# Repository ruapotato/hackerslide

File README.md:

# HackerSlide 810

A pocketable Linux handheld in the spirit of the Nokia N810: landscape screen, slide-out QWERTY keyboard with a
D-pad, an off-the-shelf CM4-format compute module on a custom carrier board. Open hardware.

> **Direction change, 2026-11-27.** `main` is turning from a Linux handheld into a **hack pad**: the same slider
> body and thumb keyboard around a powerful microcontroller instead of a Linux module, built as a radio and hardware
> multi-tool (sub-GHz, NFC, software-defined radio as far as is reasonable), with its own firmware, MicroPython, and
> music and audiobook playback. See [decisions/0009](docs/decisions/0009-hack-pad.md). The Linux handheld described
> below is complete as a design and lives on the branch [`linux-handheld`](https://github.com/ruapotato/hackerslide/tree/linux-handheld);
> everything below this note still describes it until the new design replaces it.

**Status: rev 0.1 is designed and checked as far as it can be without parts. Nothing has been built or tested:
the first boards are the test.**

**These are renders.** The enclosure, the boards and their parts are drawn from the design files; the compute
module, the battery pack, the keycap legends and what the screen shows are drawn for the picture. 131.5 x 74 x
19.35 mm; a Nokia N810 is 14 mm thick ([comparison](mechanical/renders/compare_stack.png)).

## What it is

| | |
|---|---|
| Compute | LuckFox Core3566 (RK3566, 4x Cortex-A55), swappable for other CM4-format modules within limits |
| Display | 4.0" 480 x 800 IPS, capacitive touch |
| Keyboard | 48 keys + D-pad, tact switches, I2C scanner, slides out on rails with magnet detents |
| Battery | 2800 mAh pack, USB-C charging |
| I/O | USB-C, 3.5 mm headset jack, microSD, Wi-Fi/Bluetooth on the module |
| OS | Debian/Mobian on a mainline-ish kernel (not started) |

## Where things stand

| Part | State |
|---|---|
| Carrier board | Schematic audited and revised; **fully routed**, no DRC errors. Power blocks, USB and DSI pairs laid by hand in the generator, the rest by the repository's grid router. Checked by scripts and by independent AI reviewers ([review](docs/review-2026-11-25.md)), not by a person; not built |
| Keyboard board | **Fully routed**, no DRC errors. Checked the same way; not built |
| Top plate, keyboard flex cable | Complete |
| Enclosure | Parametric model, collision-checked, with rails, travel stop, hooks and button caps; print files and assembly steps in [printing](docs/printing.md). Not printed |
| Fabrication files | Generated on demand and verified against the board files by `gerber_check.py`; `order_files.py` packs them the way JLCPCB's order page takes them ([ordering guide](bom/ordering-guide.md)). Not committed, not sent anywhere |
| Cost | First prototype, working or not, about $820-1,200, an estimate from published fees with no quote ([purchasing](bom/purchasing.md)) |
| Battery | Jauch LP675365JU, 2800 mAh, in stock at DigiKey. It is rated 2 A, so the fuse is set to 1.86 A; it has no thermistor, so the carrier's own is fitted ([purchasing](bom/purchasing.md)) |
| Bring-up | Serial console, test pads on every rail, status lamps: [bring-up plan](docs/bring-up-plan.md), [test points](docs/test-points.md), [device-tree requirements](docs/device-tree.md) |

Start with [`docs/audit-status.md`](docs/audit-status.md), then [`docs/open-questions.md`](docs/open-questions.md).

## Documents

[requirements](docs/requirements.md) · [architecture](docs/architecture.md) ·
[decisions](docs/decisions/README.md) · [pin matrix](docs/compute-pin-matrix.md) ·
[power budget](docs/power-budget.md) · [thermal](docs/thermal.md) · [carrier board](docs/carrier-board.md) ·
[keyboard](docs/keyboard.md) · [enclosure](docs/enclosure.md) · [bring-up plan](docs/bring-up-plan.md) ·
[risks](docs/risks.md) · [roadmap](docs/roadmap.md) · [audit](docs/audit-2026-11-24.md) ·
[footprint review](docs/footprint-review.md) · [pre-fab review](docs/review-2026-11-25.md) · [test points](docs/test-points.md) ·
[device tree](docs/device-tree.md) · [routing status](docs/routing-status.md) · [BOM](bom/bom.csv) · [purchasing](bom/purchasing.md) ·
[fab orders](bom/fab-orders.md) · [thinner brain](docs/thinner-brain.md) · [ordering guide](bom/ordering-guide.md) · [printing](docs/printing.md)

## Regenerating everything

The boards and the enclosure are generated from Python. Needs KiCad 9 with its libraries, Python 3, CadQuery and
OpenSCAD; details in [`docs/HANDOFF.md`](docs/HANDOFF.md), section 2.

```sh
hardware/scripts/build_all.sh                               # libraries, schematics, boards, ERC/DRC
ROUTE=1 VENV=$PWD/.venv hardware/scripts/build_all.sh       # the same, plus routing (slow; venv needs scikit-image)
hardware/scripts/render_boards.sh                           # board renders
hardware/scripts/fab_outputs.sh hardware/carrier carrier /tmp/fab   # Gerbers, drill, placement (then gerber_check.py)
cd mechanical/src && ../../.venv/bin/python hackerslide.py  # enclosure, collision check
python3 render.py ..                                        # renders
python3 ../../bom/tools/make_bom.py                         # BOM with current JLCPCB prices
python3 ../../hardware/scripts/order_files.py               # order/: Gerber zips, BOM and placement files for JLCPCB
../render/assets.sh && ../render/render_all.sh OUT_DIR      # Blender stills and clips (see mechanical/render/scene.py)
```

## How to help

Review it. The questions we most want answered are in [`docs/open-questions.md`](docs/open-questions.md); the
things a hardware reviewer should check are in [`docs/carrier-board.md`](docs/carrier-board.md) and
[`docs/footprint-review.md`](docs/footprint-review.md). Open an issue.

## Licence

- **Hardware design** (`hardware/` and `mechanical/`: schematics, boards, libraries, enclosure models and their
  exported files) is licensed under the **CERN Open Hardware Licence Version 2 - Strongly Reciprocal**
  (CERN-OHL-S-2.0), see [`LICENSES/CERN-OHL-S-2.0.txt`](LICENSES/CERN-OHL-S-2.0.txt).
- **Software and documentation** (everything else, and the Python generator scripts inside `hardware/scripts/`
  and `mechanical/src/`, which are also covered as hardware source) are licensed under the **GNU Affero General
  Public License v3.0**, see [`LICENSE`](LICENSE).

Both are strong copyleft: anyone who distributes a modified design or a product made from it must publish their
source under the same terms.

Source location for CERN-OHL-S section 4: https://github.com/ruapotato/hackerslide

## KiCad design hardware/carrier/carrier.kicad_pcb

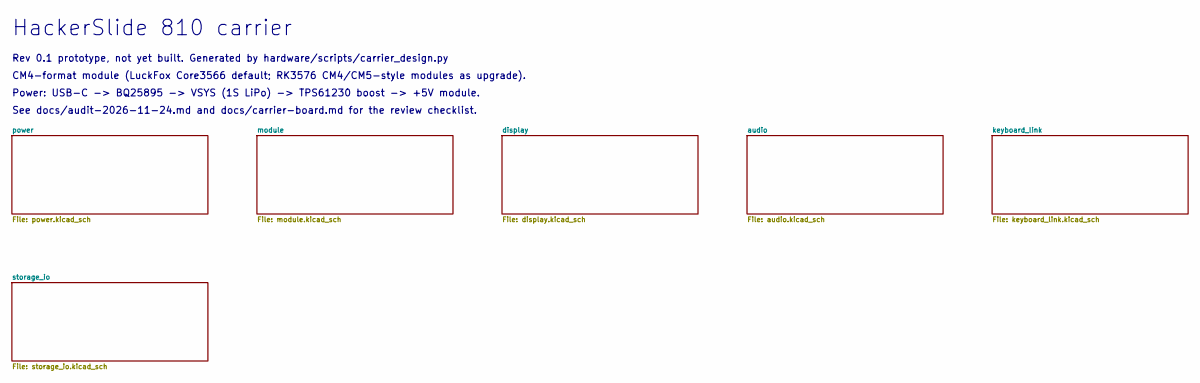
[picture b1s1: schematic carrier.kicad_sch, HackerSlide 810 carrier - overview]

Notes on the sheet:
HackerSlide 810 carrier
Rev 0.1 prototype, not yet built. Generated by hardware/scripts/carrier_design.py
CM4-format module (LuckFox Core3566 default; RK3576 CM4/CM5-style modules as upgrade).
Power: USB-C -> BQ25895 -> VSYS (1S LiPo) -> TPS61230 boost -> +5V module.
See docs/audit-2026-11-24.md and docs/carrier-board.md for the review checklist.

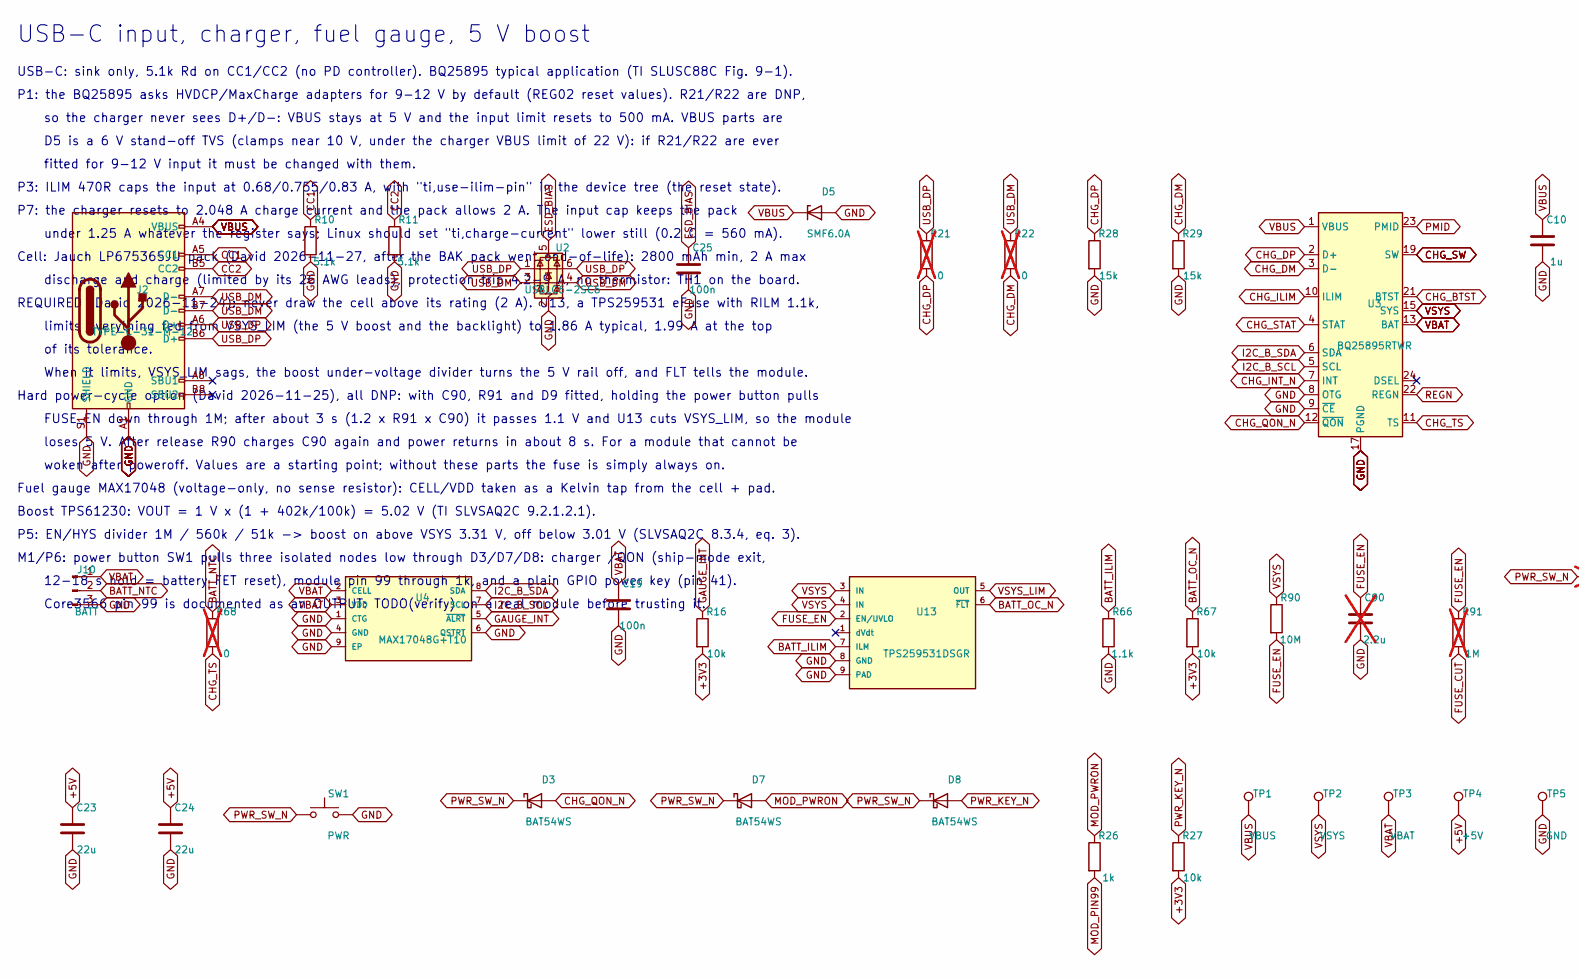
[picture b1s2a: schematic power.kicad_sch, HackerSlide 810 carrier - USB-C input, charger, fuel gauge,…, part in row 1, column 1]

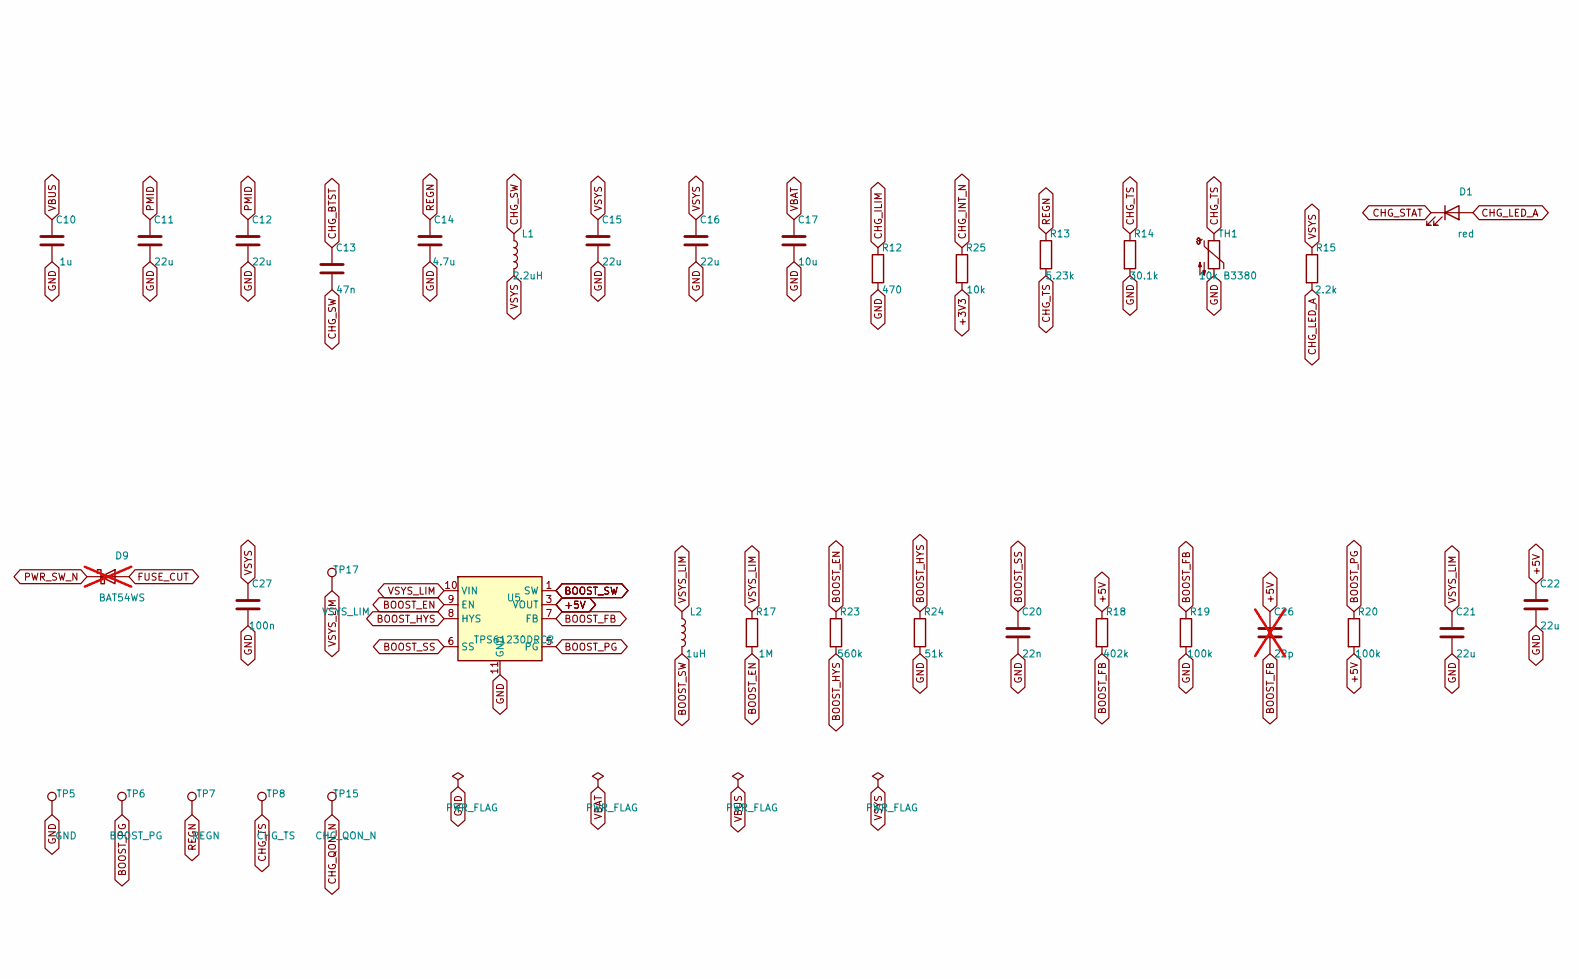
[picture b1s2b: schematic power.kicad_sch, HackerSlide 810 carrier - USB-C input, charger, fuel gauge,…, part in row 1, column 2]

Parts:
C10: 1u; C_0402_1005Metric; MPN CL05A105KA5NQNC; LCSC C52923
C11, C12, C15, C16, C21, C22, C23, C24: 22u; C_0805_2012Metric; MPN CL21A226MAQNNNE; LCSC C45783
C13: 47n; C_0402_1005Metric; MPN CL05B473KO5NNNC; LCSC C307434
C14: 4.7u; C_0603_1608Metric; MPN CL10A475KO8NNNC; LCSC C19666
C17: 10u; C_0603_1608Metric; MPN CL10A106KP8NNNC; LCSC C19702
C19, C25, C27: 100n; C_0402_1005Metric; MPN CL05B104KO5NNNC; LCSC C1525
C20: 22n; C_0402_1005Metric; MPN 0402B223K500NT; LCSC C1532
C26: 22p; C_0402_1005Metric; MPN 0402CG220J500NT; LCSC C1555; not fitted
C90: 2.2u; C_0402_1005Metric; MPN CL05A225MQ5NSNC; LCSC C12530; not fitted
D1: red; LED_0603_1608Metric; MPN KT-0603R; LCSC C2286
D3, D7, D8: BAT54WS; D_SOD-323; MPN BAT54WS-7-F; LCSC C124205
D5: SMF6.0A; D_SOD-123F; MPN SMF6.0A; LCSC C123790
D9: BAT54WS; D_SOD-323; MPN BAT54WS-7-F; LCSC C124205; not fitted
J2: TYPE-C-31-M-12; USB_C_Receptacle_HRO_TYPE-C-31-M-12; MPN TYPE-C-31-M-12; LCSC C165948
J10: BATT; Molex_SPOX_5268-03A_1x03_P2.50mm_Horizontal; MPN 22057035; LCSC C185225
L1: 2.2uH; L_Sunlord_MWSA0402S; MPN MWSA0402S-2R2MT; LCSC C408335
L2: 1uH; L_Sunlord_MWSA0402S; MPN MWSA0402S-1R0MT; LCSC C408332
R10, R11: 5.1k; R_0402_1005Metric; MPN 0402WGF5101TCE; LCSC C25905
R12: 470; R_0402_1005Metric; MPN 0402WGF4700TCE; LCSC C25117
R13: 5.23k; R_0402_1005Metric; MPN 0402WGF5231TCE; LCSC C25907
R14: 30.1k; R_0402_1005Metric; MPN 0402WGF3012TCE; LCSC C29402
R15: 2.2k; R_0402_1005Metric; MPN 0402WGF2201TCE; LCSC C25879
R16, R25, R27, R67: 10k; R_0402_1005Metric; MPN 0402WGF1002TCE; LCSC C25744
R17: 1M; R_0402_1005Metric; MPN 0402WGF1004TCE; LCSC C26083
R18: 402k; R_0402_1005Metric; MPN 0402WGF4023TCE; LCSC C25785
R19, R20: 100k; R_0402_1005Metric; MPN 0402WGF1003TCE; LCSC C25741
R21, R22, R68: 0; R_0402_1005Metric; MPN 0402WGF0000TCE; LCSC C17168; not fitted
R23: 560k; R_0402_1005Metric; MPN 0402WGF5603TCE; LCSC C132339
R24: 51k; R_0402_1005Metric; MPN 0402WGF5102TCE; LCSC C25794
R26: 1k; R_0402_1005Metric; MPN 0402WGF1001TCE; LCSC C11702
R28, R29: 15k; R_0402_1005Metric; MPN 0402WGF1502TCE; LCSC C25756
R66: 1.1k; R_0402_1005Metric; MPN 0402WGF1101TCE; LCSC C25860
R90: 10M; R_0402_1005Metric; MPN 0402WGF1005TCE; LCSC C26082
R91: 1M; R_0402_1005Metric; MPN 0402WGF1004TCE; LCSC C26083; not fitted
SW1: PWR; SW_SPST_EVQP7C; MPN EVQP7C01P; LCSC C388883
TH1: 10k B3380; R_0402_1005Metric; MPN NCP15XH103F03RC; LCSC C77131
TP1: VBUS; TestPoint_Pad_D1.0mm
TP2: VSYS; TestPoint_Pad_D1.0mm
TP3: VBAT; TestPoint_Pad_D1.0mm
TP4: +5V; TestPoint_Pad_D1.0mm
TP5: GND; TestPoint_Pad_D1.0mm
TP6: BOOST_PG; TestPoint_Pad_D1.0mm
TP7: REGN; TestPoint_Pad_D1.0mm
TP8: CHG_TS; TestPoint_Pad_D1.0mm
TP15: CHG_QON_N; TestPoint_Pad_D1.0mm
TP17: VSYS_LIM; TestPoint_Pad_D1.0mm
U2: USBLC6-2SC6; SOT-23-6; MPN USBLC6-2SC6; LCSC C7519
U3: BQ25895RTWR; Texas_RTW_WQFN-24-1EP_4x4mm_P0.5mm_EP2.7x2.7mm_ThermalVias; MPN BQ25895RTWR; LCSC C80200
U4: MAX17048G+T10; TDFN-8-1EP_2x2mm_P0.5mm_EP0.8x1.2mm; MPN MAX17048G+T10; LCSC C2682616
U5: TPS61230DRCR; Texas_S-PVSON-N10_ThermalVias; MPN TPS61230DRCR; LCSC C139626
U13: TPS259531DSGR; WSON-8-1EP_2x2mm_P0.5mm_EP0.9x1.6mm; MPN TPS259531DSGR; LCSC C2155674

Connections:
+3V3: R16.2, R25.2, R27.2, R67.2; also elsewhere on the board
+5V: C22.1, C23.1, C24.1, C26.1, R18.1, R20.2, TP4.1, U5.3 (VOUT), U5.4 (VOUT); also elsewhere on the board
BATT_ILIM: R66.1, U13.7 (ILM)
BATT_NTC: J10.2, R68.1
BATT_OC_N: R67.1, U13.6 (~FLT); also elsewhere on the board
BOOST_EN: R17.2, R23.1, U5.9 (EN)
BOOST_FB: C26.2, R18.2, R19.1, U5.7 (FB)
BOOST_HYS: R23.2, R24.1, U5.8 (HYS)
BOOST_PG: R20.1, TP6.1, U5.5 (PG)
BOOST_SS: C20.1, U5.6 (SS)
BOOST_SW: L2.2, U5.1 (SW), U5.2 (SW)
CC1: J2.A5 (CC1), R10.1
CC2: J2.B5 (CC2), R11.1
CHG_BTST: C13.1, U3.21 (BTST)
CHG_DM: R22.2, R29.1, U3.3 (D-)
CHG_DP: R21.2, R28.1, U3.2 (D+)
CHG_ILIM: R12.1, U3.10 (ILIM)
CHG_INT_N: R25.1, U3.7 (INT); also elsewhere on the board
CHG_LED_A: D1.2 (A), R15.2
CHG_QON_N: D3.2 (A), TP15.1, U3.12 (~QON)
CHG_STAT: D1.1 (K), U3.4 (STAT)
CHG_SW: C13.2, L1.1, U3.19 (SW), U3.20 (SW)
CHG_TS: R13.2, R14.1, R68.2, TH1.1, TP8.1, U3.11 (TS)
ESD_BIAS: C25.1, U2.5 (VBUS)
FUSE_CUT: D9.2 (A), R91.2
FUSE_EN: C90.1, R90.2, R91.1, U13.2 (EN/UVLO)
GAUGE_INT: R16.1, U4.5 (~ALRT); also elsewhere on the board
GND: C10.2, C11.2, C12.2, C14.2, C15.2, C16.2, C17.2, C19.2, C20.2, C21.2, C22.2, C23.2, C24.2, C25.2, C27.2, C90.2, D5.2 (A), J2.A1 (GND), J2.A12 (GND), J2.B1 (GND), J2.B12 (GND), J2.S1 (SHIELD), J10.3, R10.2, R11.2, R12.2, R14.2, R19.2, R24.2, R28.2, R29.2, R66.2, SW1.2, TH1.2, TP5.1, U2.2 (GND), U3.8 (OTG), U3.9 (~CE), U3.17 (PGND), U3.18 (PGND), U3.25 (PGND), U4.1 (CTG), U4.4 (GND), U4.6 (QSTRT), U4.9 (EP), U5.11 (GND), U13.8 (GND), U13.9 (PAD); also elsewhere on the board
I2C_B_SCL: U3.5 (SCL), U4.7 (SCL); also elsewhere on the board
I2C_B_SDA: U3.6 (SDA), U4.8 (SDA); also elsewhere on the board
MOD_PIN99: R26.2; also elsewhere on the board
MOD_PWRON: D7.2 (A), R26.1
PMID: C11.1, C12.1, U3.23 (PMID)
PWR_KEY_N: D8.2 (A), R27.1; also elsewhere on the board
PWR_SW_N: D3.1 (K), D7.1 (K), D8.1 (K), D9.1 (K), SW1.1
REGN: C14.1, R13.1, TP7.1, U3.22 (REGN)
USB_DM: J2.A7 (D-), J2.B7 (D-), R22.1, U2.3 (I/O2), U2.4 (I/O2); also elsewhere on the board
USB_DP: J2.A6 (D+), J2.B6 (D+), R21.1, U2.1 (I/O1), U2.6 (I/O1); also elsewhere on the board
VBAT: C17.1, C19.1, J10.1, TP3.1, U3.13 (BAT), U3.14 (BAT), U4.2 (CELL), U4.3 (VDD)
VBUS: C10.1, D5.1 (K), J2.A4 (VBUS), J2.A9 (VBUS), J2.B4 (VBUS), J2.B9 (VBUS), TP1.1, U3.1 (VBUS)
VSYS: C15.1, C16.1, C27.1, L1.2, R15.1, R90.1, TP2.1, U3.15 (SYS), U3.16 (SYS), U13.3 (IN), U13.4 (IN)
VSYS_LIM: C21.1, L2.1, R17.1, TP17.1, U5.10 (VIN), U13.5 (OUT); also elsewhere on the board

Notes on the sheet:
USB-C input, charger, fuel gauge, 5 V boost
USB-C: sink only, 5.1k Rd on CC1/CC2 (no PD controller). BQ25895 typical application (TI SLUSC88C Fig. 9-1).
P1: the BQ25895 asks HVDCP/MaxCharge adapters for 9-12 V by default (REG02 reset values). R21/R22 are DNP,
so the charger never sees D+/D-: VBUS stays at 5 V and the input limit resets to 500 mA. VBUS parts are
D5 is a 6 V stand-off TVS (clamps near 10 V, under the charger VBUS limit of 22 V): if R21/R22 are ever
fitted for 9-12 V input it must be changed with them.
P3: ILIM 470R caps the input at 0.68/0.755/0.83 A, with "ti,use-ilim-pin" in the device tree (the reset state).
P7: the charger resets to 2.048 A charge current and the pack allows 2 A. The input cap keeps the pack
under 1.25 A whatever the register says; Linux should set "ti,charge-current" lower still (0.2 C = 560 mA).
Cell: Jauch LP675365JU pack (David 2026-11-27, after the BAK pack went end-of-life): 2800 mAh min, 2 A max
discharge and charge (limited by its 26 AWG leads), protection trip 4.2-9 A, no thermistor: TH1 on the board.
REQUIRED (David 2026-11-24): never draw the cell above its rating (2 A). U13, a TPS259531 eFuse with RILM 1.1k,
limits everything fed from VSYS_LIM (the 5 V boost and the backlight) to 1.86 A typical, 1.99 A at the top
of its tolerance.
When it limits, VSYS_LIM sags, the boost under-voltage divider turns the 5 V rail off, and FLT tells the module.
Hard power-cycle option (David 2026-11-25), all DNP: with C90, R91 and D9 fitted, holding the power button pulls
FUSE_EN down through 1M; after about 3 s (1.2 x R91 x C90) it passes 1.1 V and U13 cuts VSYS_LIM, so the module
loses 5 V. After release R90 charges C90 again and power returns in about 8 s. For a module that cannot be
woken after poweroff. Values are a starting point; without these parts the fuse is simply always on.
Fuel gauge MAX17048 (voltage-only, no sense resistor): CELL/VDD taken as a Kelvin tap from the cell + pad.
Boost TPS61230: VOUT = 1 V x (1 + 402k/100k) = 5.02 V (TI SLVSAQ2C 9.2.1.2.1).
P5: EN/HYS divider 1M / 560k / 51k -> boost on above VSYS 3.31 V, off below 3.01 V (SLVSAQ2C 8.3.4, eq. 3).
M1/P6: power button SW1 pulls three isolated nodes low through D3/D7/D8: charger /QON (ship-mode exit,
12-18 s hold = battery FET reset), module pin 99 through 1k, and a plain GPIO power key (pin 41).
Core3566 pin 99 is documented as an OUTPUT: TODO(verify) on a real module before trusting it.

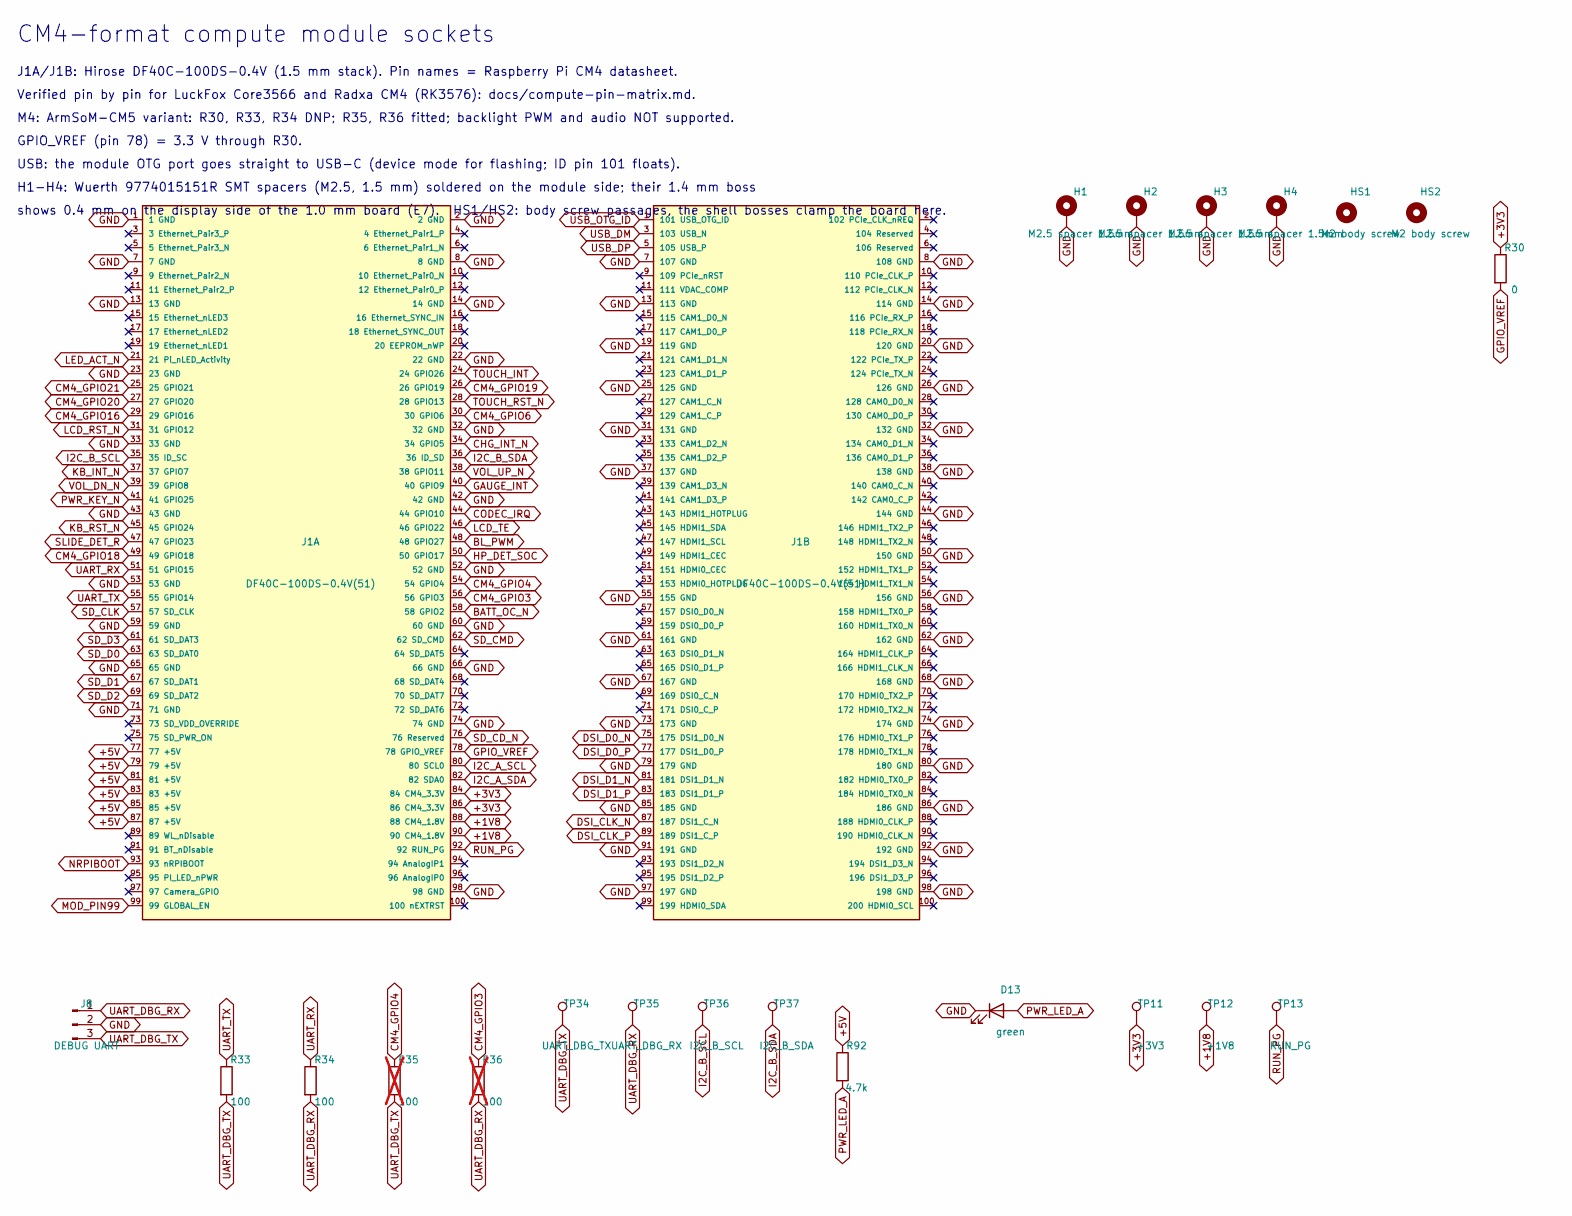
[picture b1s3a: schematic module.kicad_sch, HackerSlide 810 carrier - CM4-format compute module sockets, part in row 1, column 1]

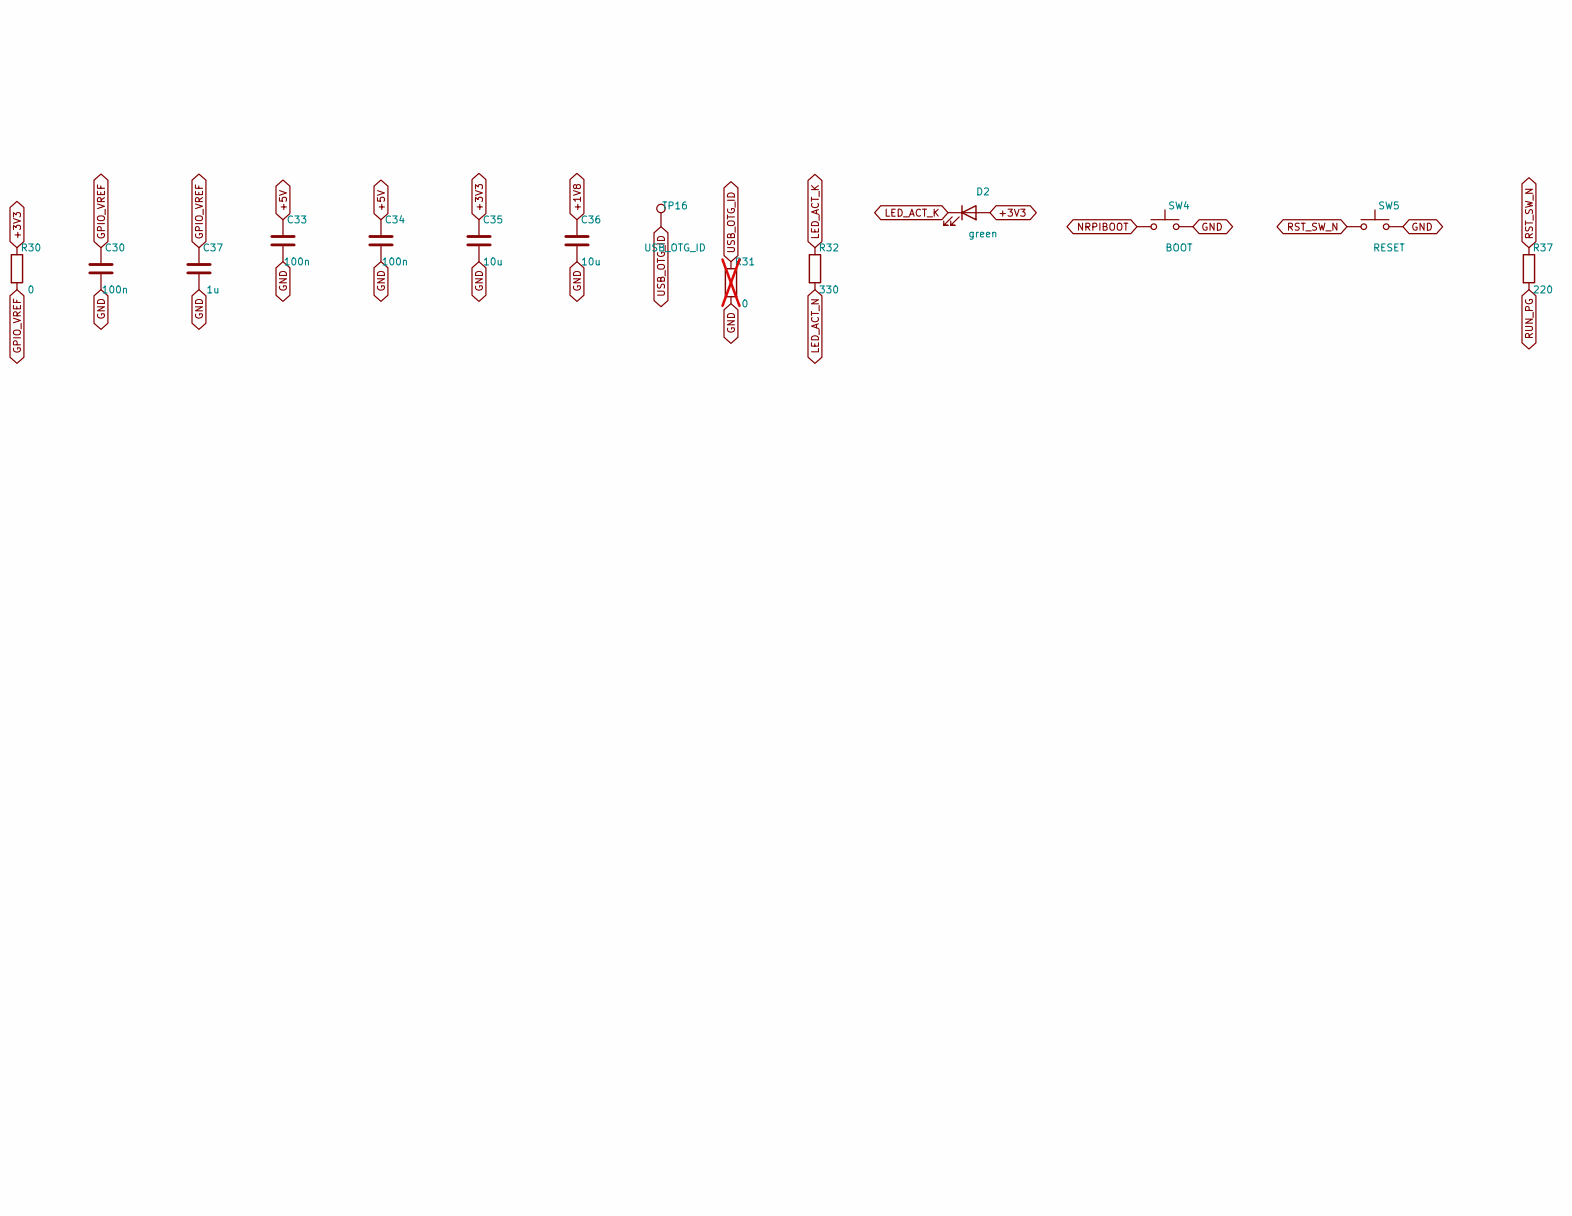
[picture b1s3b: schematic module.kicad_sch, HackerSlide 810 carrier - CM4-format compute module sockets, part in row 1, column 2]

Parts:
C30, C33, C34: 100n; C_0402_1005Metric; MPN CL05B104KO5NNNC; LCSC C1525
C35, C36: 10u; C_0603_1608Metric; MPN CL10A106KP8NNNC; LCSC C19702
C37: 1u; C_0402_1005Metric; MPN CL05A105KA5NQNC; LCSC C52923
D2, D13: green; LED_0603_1608Metric; MPN KT-0603G; LCSC C12624
H1, H2, H3, H4: M2.5 spacer 1.5mm; Mounting_Wuerth_WA-SMSI-M2.5_H1.5mm_9774015151R; MPN 9774015151R; LCSC C5353804
HS1, HS2: M2 body screw; MountingHole_M2_NPTH_BodyScrew
J1A, J1B: DF40C-100DS-0.4V(51); Hirose_DF40C-100DS-0.4V_2x50_P0.4mm; MPN DF40C-100DS-0.4V(51); LCSC C597931
J8: DEBUG UART; JST_SH_SM03B-SRSS-TB_1x03-1MP_P1.00mm_Horizontal; MPN SM03B-SRSS-TB(LF)(SN); LCSC C160403
R30: 0; R_0402_1005Metric; MPN 0402WGF0000TCE; LCSC C17168
R31: 0; R_0402_1005Metric; MPN 0402WGF0000TCE; LCSC C17168; not fitted
R32: 330; R_0402_1005Metric; MPN 0402WGF3300TCE; LCSC C25104
R33, R34: 100; R_0402_1005Metric; MPN 0402WGF1000TCE; LCSC C25076
R35, R36: 100; R_0402_1005Metric; MPN 0402WGF1000TCE; LCSC C25076; not fitted
R37: 220; R_0402_1005Metric; MPN 0402WGF2200TCE; LCSC C25091
R92: 4.7k; R_0402_1005Metric; MPN 0402WGF4701TCE; LCSC C25900
SW4: BOOT; SW_SPST_EVQP7C; MPN EVQP7C01P; LCSC C388883
SW5: RESET; SW_SPST_EVQP7C; MPN EVQP7C01P; LCSC C388883
TP11: +3V3; TestPoint_Pad_D1.0mm
TP12: +1V8; TestPoint_Pad_D1.0mm
TP13: RUN_PG; TestPoint_Pad_D1.0mm
TP16: USB_OTG_ID; TestPoint_Pad_D1.0mm
TP34: UART_DBG_TX; TestPoint_Pad_D1.0mm
TP35: UART_DBG_RX; TestPoint_Pad_D1.0mm
TP36: I2C_B_SCL; TestPoint_Pad_D1.0mm
TP37: I2C_B_SDA; TestPoint_Pad_D1.0mm

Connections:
+1V8: C36.1, J1A.88 (88 CM4_1.8V), J1A.90 (90 CM4_1.8V), TP12.1; also elsewhere on the board
+3V3: C35.1, D2.2 (A), J1A.84 (84 CM4_3.3V), J1A.86 (86 CM4_3.3V), R30.1, TP11.1; also elsewhere on the board
+5V: C33.1, C34.1, J1A.77 (77 +5V), J1A.79 (79 +5V), J1A.81 (81 +5V), J1A.83 (83 +5V), J1A.85 (85 +5V), J1A.87 (87 +5V), R92.1; also elsewhere on the board
BATT_OC_N: J1A.58 (58 GPIO2); also elsewhere on the board
BL_PWM: J1A.48 (48 GPIO27); also elsewhere on the board
CHG_INT_N: J1A.34 (34 GPIO5); also elsewhere on the board
CM4_GPIO3: J1A.56 (56 GPIO3), R36.1
CM4_GPIO4: J1A.54 (54 GPIO4), R35.1
CM4_GPIO6: J1A.30 (30 GPIO6); also elsewhere on the board
CM4_GPIO16: J1A.29 (29 GPIO16); also elsewhere on the board
CM4_GPIO18: J1A.49 (49 GPIO18); also elsewhere on the board
CM4_GPIO19: J1A.26 (26 GPIO19); also elsewhere on the board
CM4_GPIO20: J1A.27 (27 GPIO20); also elsewhere on the board
CM4_GPIO21: J1A.25 (25 GPIO21); also elsewhere on the board
CODEC_IRQ: J1A.44 (44 GPIO10); also elsewhere on the board
DSI_CLK_N: J1B.87 (187 DSI1_C_N); also elsewhere on the board
DSI_CLK_P: J1B.89 (189 DSI1_C_P); also elsewhere on the board
DSI_D0_N: J1B.75 (175 DSI1_D0_N); also elsewhere on the board
DSI_D0_P: J1B.77 (177 DSI1_D0_P); also elsewhere on the board
DSI_D1_N: J1B.81 (181 DSI1_D1_N); also elsewhere on the board
DSI_D1_P: J1B.83 (183 DSI1_D1_P); also elsewhere on the board
GAUGE_INT: J1A.40 (40 GPIO9); also elsewhere on the board
GND: C30.2, C33.2, C34.2, C35.2, C36.2, C37.2, D13.1 (K), H1.1, H2.1, H3.1, H4.1, J1A.1 (1 GND), J1A.2 (2 GND), J1A.7 (7 GND), J1A.8 (8 GND), J1A.13 (13 GND), J1A.14 (14 GND), J1A.22 (22 GND), J1A.23 (23 GND), J1A.32 (32 GND), J1A.33 (33 GND), J1A.42 (42 GND), J1A.43 (43 GND), J1A.52 (52 GND), J1A.53 (53 GND), J1A.59 (59 GND), J1A.60 (60 GND), J1A.65 (65 GND), J1A.66 (66 GND), J1A.71 (71 GND), J1A.74 (74 GND), J1A.98 (98 GND), J1B.7 (107 GND), J1B.8 (108 GND), J1B.13 (113 GND), J1B.14 (114 GND), J1B.19 (119 GND), J1B.20 (120 GND), J1B.25 (125 GND), J1B.26 (126 GND), J1B.31 (131 GND), J1B.32 (132 GND), J1B.37 (137 GND), J1B.38 (138 GND), J1B.44 (144 GND), J1B.50 (150 GND), J1B.55 (155 GND), J1B.56 (156 GND), J1B.61 (161 GND), J1B.62 (162 GND), J1B.67 (167 GND), J1B.68 (168 GND), J1B.73 (173 GND), J1B.74 (174 GND), J1B.79 (179 GND), J1B.80 (180 GND), J1B.85 (185 GND), J1B.86 (186 GND), J1B.91 (191 GND), J1B.92 (192 GND), J1B.97 (197 GND), J1B.98 (198 GND), J8.2, R31.2, SW4.2, SW5.2; also elsewhere on the board
GPIO_VREF: C30.1, C37.1, J1A.78 (78 GPIO_VREF), R30.2
HP_DET_SOC: J1A.50 (50 GPIO17); also elsewhere on the board
I2C_A_SCL: J1A.80 (80 SCL0); also elsewhere on the board
I2C_A_SDA: J1A.82 (82 SDA0); also elsewhere on the board
I2C_B_SCL: J1A.35 (35 ID_SC), TP36.1; also elsewhere on the board
I2C_B_SDA: J1A.36 (36 ID_SD), TP37.1; also elsewhere on the board
KB_INT_N: J1A.37 (37 GPIO7); also elsewhere on the board
KB_RST_N: J1A.45 (45 GPIO24); also elsewhere on the board
LCD_RST_N: J1A.31 (31 GPIO12); also elsewhere on the board
LCD_TE: J1A.46 (46 GPIO22); also elsewhere on the board
LED_ACT_K: D2.1 (K), R32.1
LED_ACT_N: J1A.21 (21 Pi_nLED_Activity), R32.2
MOD_PIN99: J1A.99 (99 GLOBAL_EN); also elsewhere on the board
NRPIBOOT: J1A.93 (93 nRPIBOOT), SW4.1
PWR_KEY_N: J1A.41 (41 GPIO25); also elsewhere on the board
PWR_LED_A: D13.2 (A), R92.2
RST_SW_N: R37.1, SW5.1
RUN_PG: J1A.92 (92 RUN_PG), R37.2, TP13.1
SD_CD_N: J1A.76 (76 Reserved); also elsewhere on the board
SD_CLK: J1A.57 (57 SD_CLK); also elsewhere on the board
SD_CMD: J1A.62 (62 SD_CMD); also elsewhere on the board
SD_D0: J1A.63 (63 SD_DAT0); also elsewhere on the board
SD_D1: J1A.67 (67 SD_DAT1); also elsewhere on the board
SD_D2: J1A.69 (69 SD_DAT2); also elsewhere on the board
SD_D3: J1A.61 (61 SD_DAT3); also elsewhere on the board
SLIDE_DET_R: J1A.47 (47 GPIO23); also elsewhere on the board
TOUCH_INT: J1A.24 (24 GPIO26); also elsewhere on the board
TOUCH_RST_N: J1A.28 (28 GPIO13); also elsewhere on the board
UART_DBG_RX: J8.1, R34.2, R36.2, TP35.1
UART_DBG_TX: J8.3, R33.2, R35.2, TP34.1
UART_RX: J1A.51 (51 GPIO15), R34.1
UART_TX: J1A.55 (55 GPIO14), R33.1
USB_DM: J1B.3 (103 USB_N); also elsewhere on the board
USB_DP: J1B.5 (105 USB_P); also elsewhere on the board
USB_OTG_ID: J1B.1 (101 USB_OTG_ID), R31.1, TP16.1
VOL_DN_N: J1A.39 (39 GPIO8); also elsewhere on the board
VOL_UP_N: J1A.38 (38 GPIO11); also elsewhere on the board

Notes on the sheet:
CM4-format compute module sockets
J1A/J1B: Hirose DF40C-100DS-0.4V (1.5 mm stack). Pin names = Raspberry Pi CM4 datasheet.
Verified pin by pin for LuckFox Core3566 and Radxa CM4 (RK3576): docs/compute-pin-matrix.md.
M4: ArmSoM-CM5 variant: R30, R33, R34 DNP; R35, R36 fitted; backlight PWM and audio NOT supported.
GPIO_VREF (pin 78) = 3.3 V through R30.
USB: the module OTG port goes straight to USB-C (device mode for flashing; ID pin 101 floats).
H1-H4: Wuerth 9774015151R SMT spacers (M2.5, 1.5 mm) soldered on the module side; their 1.4 mm boss
shows 0.4 mm on the display side of the 1.0 mm board (E7). HS1/HS2: body screw passages, the shell bosses clamp the board here.

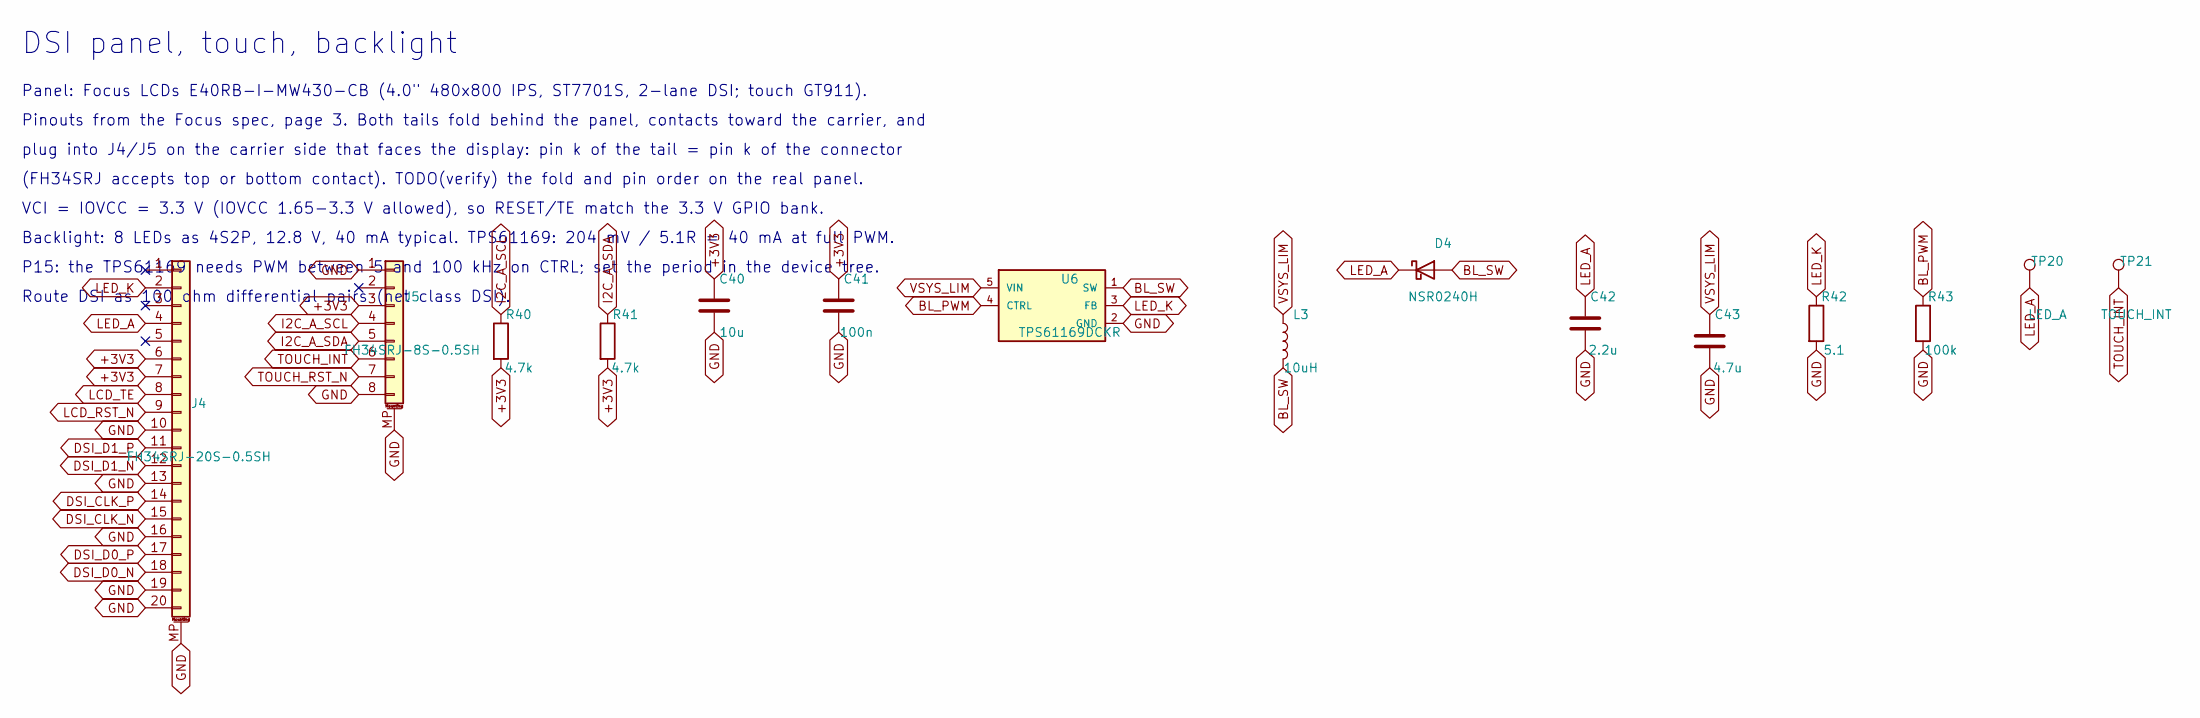
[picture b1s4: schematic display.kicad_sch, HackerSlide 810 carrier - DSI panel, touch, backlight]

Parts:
C40: 10u; C_0603_1608Metric; MPN CL10A106KP8NNNC; LCSC C19702
C41: 100n; C_0402_1005Metric; MPN CL05B104KO5NNNC; LCSC C1525
C42: 2.2u; C_0805_2012Metric; MPN CL21A225KBFNNNE; LCSC C307528
C43: 4.7u; C_0402_1005Metric; MPN CL05A475MP5NRNC; LCSC C23733
D4: NSR0240H; D_SOD-323; MPN NSR0240HT1G; LCSC C152519
J4: FH34SRJ-20S-0.5SH; Hirose_FH34SRJ-20S-0.5SH_1x20-1MP_P0.50mm_Horizontal; MPN FH34SRJ-20S-0.5SH(50); LCSC C2802370
J5: FH34SRJ-8S-0.5SH; Hirose_FH34SRJ-8S-0.5SH_1x08-1MP_P0.50mm_Horizontal; MPN FH34SRJ-8S-0.5SH(50); LCSC C88372
L3: 10uH; L_Sunlord_SWPA4030S; MPN SWPA4030S100MT; LCSC C38117
R40, R41: 4.7k; R_0402_1005Metric; MPN 0402WGF4701TCE; LCSC C25900
R42: 5.1; R_0402_1005Metric; MPN 0402WGF510KTCE; LCSC C25128
R43: 100k; R_0402_1005Metric; MPN 0402WGF1003TCE; LCSC C25741
TP20: LED_A; TestPoint_Pad_D1.0mm
TP21: TOUCH_INT; TestPoint_Pad_D1.0mm
U6: TPS61169DCKR; SOT-353_SC-70-5; MPN TPS61169DCKR; LCSC C71045

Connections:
+3V3: C40.1, C41.1, J4.6, J4.7, J5.3, R40.2, R41.2; also elsewhere on the board
BL_PWM: R43.1, U6.4 (CTRL); also elsewhere on the board
BL_SW: D4.2 (A), L3.2, U6.1 (SW)
DSI_CLK_N: J4.15; also elsewhere on the board
DSI_CLK_P: J4.14; also elsewhere on the board
DSI_D0_N: J4.18; also elsewhere on the board
DSI_D0_P: J4.17; also elsewhere on the board
DSI_D1_N: J4.12; also elsewhere on the board
DSI_D1_P: J4.11; also elsewhere on the board
GND: C40.2, C41.2, C42.2, C43.2, J4.10, J4.13, J4.16, J4.19, J4.20, J4.MP (MountPin), J5.1, J5.8, J5.MP (MountPin), R42.2, R43.2, U6.2 (GND); also elsewhere on the board
I2C_A_SCL: J5.4, R40.1; also elsewhere on the board
I2C_A_SDA: J5.5, R41.1; also elsewhere on the board
LCD_RST_N: J4.9; also elsewhere on the board
LCD_TE: J4.8; also elsewhere on the board
LED_A: C42.1, D4.1 (K), J4.4, TP20.1
LED_K: J4.2, R42.1, U6.3 (FB)
TOUCH_INT: J5.6, TP21.1; also elsewhere on the board
TOUCH_RST_N: J5.7; also elsewhere on the board
VSYS_LIM: C43.1, L3.1, U6.5 (VIN); also elsewhere on the board

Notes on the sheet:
DSI panel, touch, backlight
Panel: Focus LCDs E40RB-I-MW430-CB (4.0" 480x800 IPS, ST7701S, 2-lane DSI; touch GT911).
Pinouts from the Focus spec, page 3. Both tails fold behind the panel, contacts toward the carrier, and
plug into J4/J5 on the carrier side that faces the display: pin k of the tail = pin k of the connector
(FH34SRJ accepts top or bottom contact). TODO(verify) the fold and pin order on the real panel.
VCI = IOVCC = 3.3 V (IOVCC 1.65-3.3 V allowed), so RESET/TE match the 3.3 V GPIO bank.
Backlight: 8 LEDs as 4S2P, 12.8 V, 40 mA typical. TPS61169: 204 mV / 5.1R = 40 mA at full PWM.
P15: the TPS61169 needs PWM between 5 and 100 kHz on CTRL; set the period in the device tree.
Route DSI as 100 ohm differential pairs (net class DSI).

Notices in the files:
hardware/carrier/audio.kicad_sch:
HackerSlide project (AGPL-3.0)
hardware/carrier/carrier.kicad_pcb:
github.com/ruapotato/hackerslide  CERN-OHL-S-2.0
hardware/keyboard/keyboard.kicad_pcb:
HackerSlide 810 keyboard Alps SKSW rev 0.1  CERN-OHL-S-2.0
